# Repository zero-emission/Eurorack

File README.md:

# Eurorack
A collection of open hardware projects for Eurorack

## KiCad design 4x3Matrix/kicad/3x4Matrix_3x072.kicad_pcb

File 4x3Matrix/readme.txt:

A simple 4 in, 3 out Matrix mixer in 10HP.

It's designed to be an easy build as a first SMD project, with 0805 resistors with plenty of space inbetween.

The four inputs can be mixed in a three different ways for three different outputs.

The mixer is DC coupled, so can be used for both CV and audio.

Please double check IC orientation: TL072 pin 1 is down, TL074 pin 1 is up (Skewed side of the IC)
Some examples:

- Mix four cv signals to three different outputs
- Create feedback loops, patching one output back into an input. 
By patching multiple feedback loops you can create complex audio signals and waveshaping. 
Patching effects like delays inbetween can produce infinite feedback.

- For output A turn down input 3 and 4. For output B turn down input 1 and 2. Now you have two independent 2 channel mixers. 
You could use one as a CV attenuator and the other for mixing audio.

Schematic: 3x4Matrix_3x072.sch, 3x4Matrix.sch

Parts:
A_1, A_2, A_3, A_4: A100K; Potentiometer_Alpha_RD901F-40-00D_Single_Vertical
B_1, B_2, B_3, B_4: A100K; Potentiometer_Alpha_RD901F-40-00D_Single_Vertical
C1, C2: 10uF; CP_Radial_D5.0mm_P2.50mm
C3, C4, C5, C6, C7, C8: 100nF; C_0805_2012Metric
C_1, C_2, C_3, C_4: A100K; Potentiometer_Alpha_RD901F-40-00D_Single_Vertical
D1, D2: 1N4004; D_DO-41_SOD81_P10.16mm_Horizontal
IN1, IN2, IN3, IN4: AudioJack; Jack_3.5mm_QingPu_WQP-PJ398SM_Vertical_CircularHoles
OUTA1: AudioJack; Jack_3.5mm_QingPu_WQP-PJ398SM_Vertical_CircularHoles
OUTB1: AudioJack; Jack_3.5mm_QingPu_WQP-PJ398SM_Vertical_CircularHoles
OUTC1: AudioJack; Jack_3.5mm_QingPu_WQP-PJ398SM_Vertical_CircularHoles
R1, R2, R3, R4, R5, R6, R7, R8, R9, R10, R11, R12, R13, R14, R15, R16, R17, R18, R19, R20, R21: 100k; R_0805_2012Metric
R22, R23, R24: 1k; R_0805_2012Metric
SV2: EURO_POWER_HEADERREGULAR; PinHeader_2x05_P2.54mm_Vertical
U1, U2, U3: TL072_SMD; SOIC-8_3.9x4.9mm_P1.27mm

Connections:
/+12UP1: D1.2 (A), SV2.1, SV2.2
/-12UP1: D2.1 (K), SV2.9, SV2.10
/C-11: R3.1, R4.1, R9.2, R18.1, R21.1, U1.2 (-)
/N$1: A_3.2, R1.2
/N$2: B_3.2, R2.2
/N$3: C_3.2, R3.2
/N$4: C_2.2, R4.2
/N$5: B_2.2, R5.2
/N$6: A_2.2, R6.2
/N$7: B_1.2, R8.2
/N$8: C_1.2, R18.2
/N$9: A_1.2, R7.2
/N$10: A_4.3, B_4.3, C_4.3, IN4.T
/N$11: OUTC1.T, R22.1
/N$12: C1.2, C3.2, C5.2, C7.2, D2.2 (A), U1.4 (V-), U2.4 (V-), U3.4 (V-)
/N$13: A_4.2, R19.2
/N$14: B_4.2, R20.2
/N$15: C_4.2, R21.2
/N$16: OUTB1.T, R23.1
/N$17: OUTA1.T, R24.1
/N$18: R1.1, R6.1, R7.1, R15.2, R19.1, U3.2 (-)
/N$21: A_3.3, B_3.3, C_3.3, IN3.T
/N$22: A_2.3, B_2.3, C_2.3, IN2.T
/N$23: A_1.3, B_1.3, C_1.3, IN1.T
/N$24: R12.1, R13.2, U2.1
/N$25: R10.1, R11.2, U1.6 (-)
/N$26: R2.1, R5.1, R8.1, R12.2, R20.1, U2.2 (-)
/N$27: R11.1, R22.2, U1.7
/N$28: R13.1, R14.2, U2.6 (-)
/N$29: R14.1, R23.2, U2.7
/N$32: R16.1, R17.2, U3.6 (-)
/N$33: R17.1, R24.2, U3.7
/N$35: C2.1, C4.1, C6.1, C8.1, D1.1 (K), U1.8 (V+), U2.8 (V+), U3.8 (V+)
/PIN1: R9.1, R10.2, U1.1
/PINN1: R15.1, R16.2, U3.1
GND: A_1.1, A_2.1, A_3.1, A_4.1, B_1.1, B_2.1, B_3.1, B_4.1, C1.1, C2.2, C3.1, C4.2, C5.1, C6.2, C7.1, C8.2, C_1.1, C_2.1, C_3.1, C_4.1, IN1.S, IN2.S, IN3.S, IN4.S, OUTA1.S, OUTB1.S, OUTC1.S, SV2.3, SV2.4, SV2.5, SV2.6, SV2.7, SV2.8, U1.3 (+), U1.5 (+), U2.3 (+), U2.5 (+), U3.3 (+), U3.5 (+)

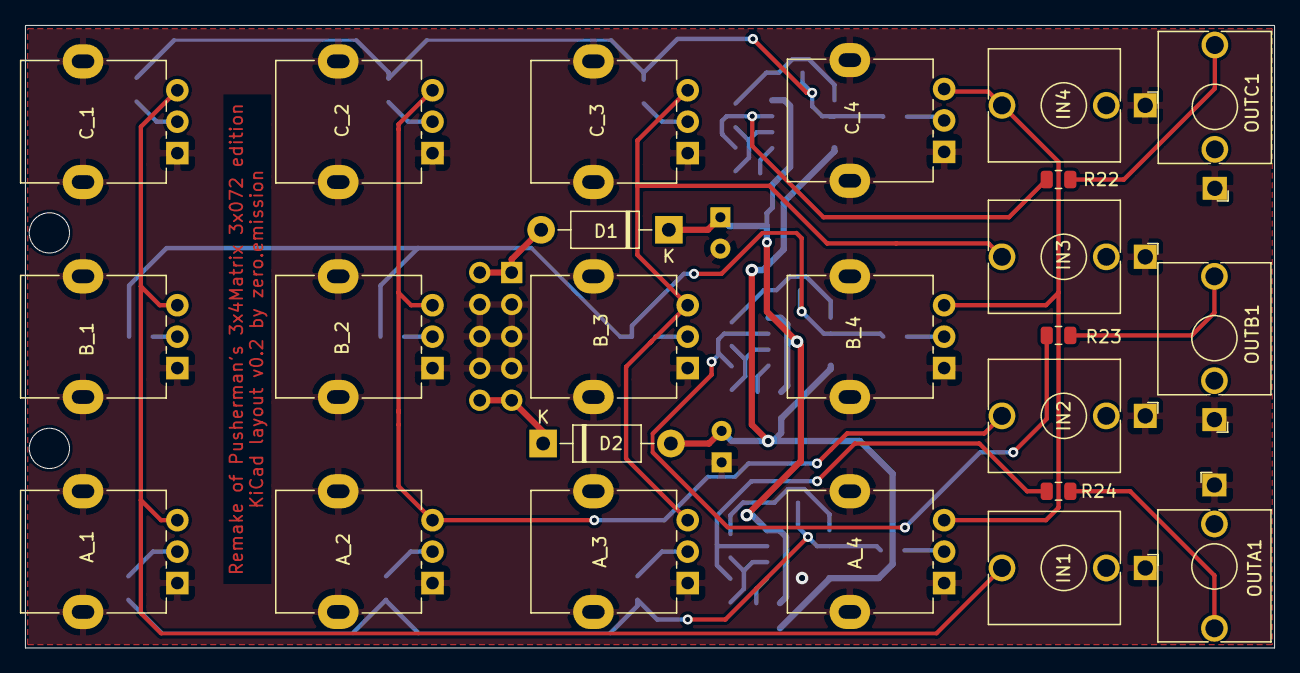
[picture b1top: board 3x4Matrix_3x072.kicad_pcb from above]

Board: 2 copper layers, 99.4 x 49.5 mm, 59 parts (0 on the bottom side), 36 nets.

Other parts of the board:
@HOLE0, @HOLE1: (no value)

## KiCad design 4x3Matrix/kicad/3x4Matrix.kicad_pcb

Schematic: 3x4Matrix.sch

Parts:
A1, A2, A3, A4: A100K; Potentiometer_Alpha_RD901F-40-00D_Single_Vertical
B1, B2, B3, B4: A100K; Potentiometer_Alpha_RD901F-40-00D_Single_Vertical
C1, C9, C10, C11: 100nF; SPARKFUN_0805
C7, C8: 10uF; SPARKFUN-CAPACITORS_CPOL-RADIAL-10UF-25V
C-1-34, C-2, C-3, C-4: A100K; Potentiometer_Alpha_RD901F-40-00D_Single_Vertical
D3, D4: 1N4004; _MOD_DIODE_DO41-10
M1, M2, M3, M4: AudioJack; Jack_3.5mm_QingPu_WQP-PJ398SM_Vertical_CircularHoles
MAA34: AudioJack; Jack_3.5mm_QingPu_WQP-PJ398SM_Vertical_CircularHoles
MB34: AudioJack; Jack_3.5mm_QingPu_WQP-PJ398SM_Vertical_CircularHoles
MCC34: AudioJack; Jack_3.5mm_QingPu_WQP-PJ398SM_Vertical_CircularHoles
R1, R2, R3, R4, R5, R6, R7, R8, R9, R10, R11, R12, R13, R14, R15, R16, R17, R18, R19, R20, R21: 100k; SPARKFUN-PASSIVES_0805
R22, R23, R24: 1k; SPARKFUN-PASSIVES_0805
SV2: EURO_POWER_HEADERREGULAR; PinHeader_2x05_P2.54mm_Vertical
U1: TL074_SMD; SOIC-14_3.9x8.7mm_P1.27mm
U2: TL072_SMD; SOIC-8_3.9x4.9mm_P1.27mm

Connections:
/+12UP1: D3.A, SV2.1, SV2.2
/-12UP1: D4.C, SV2.9, SV2.10
/C-11: R3.1, R4.1, R9.2, R18.1, R21.1, U1.2
/N$1: A3.2, R1.2
/N$2: B3.2, R2.2
/N$3: C-3.2, R3.2
/N$4: C-2.2, R4.2
/N$5: B2.2, R5.2
/N$6: A2.2, R6.2
/N$7: B1.2, R8.2
/N$8: C-1-34.2, R18.2
/N$9: A1.2, R7.2
/N$10: A4.3, B4.3, C-4.3, M4.T
/N$11: MCC34.T, R22.1
/N$12: C1.2, C8.2, C10.2, D4.A, U1.11, U2.4 (V-)
/N$13: A4.2, R19.2
/N$14: B4.2, R20.2
/N$15: C-4.2, R21.2
/N$16: MB34.T, R23.1
/N$17: MAA34.T, R24.1
/N$18: R1.1, R6.1, R7.1, R15.2, R19.1, U2.2 (-)
/N$21: A3.3, B3.3, C-3.3, M3.T
/N$22: A2.3, B2.3, C-2.3, M2.T
/N$23: A1.3, B1.3, C-1-34.3, M1.T
/N$24: R12.1, R13.2, U1.8
/N$25: R10.1, R11.2, U1.6
/N$26: R2.1, R5.1, R8.1, R12.2, R20.1, U1.9
/N$27: R11.1, R22.2, U1.7
/N$28: R13.1, R14.2, U1.13
/N$29: R14.1, R23.2, U1.14
/N$32: R16.1, R17.2, U2.6 (-)
/N$33: R17.1, R24.2, U2.7
/N$35: C7.1, C9.1, C11.1, D3.C, U1.4, U2.8 (V+)
/PIN1: R9.1, R10.2, U1.1
/PINN1: R15.1, R16.2, U2.1
GND: A1.1, A2.1, A3.1, A4.1, B1.1, B2.1, B3.1, B4.1, C1.1, C7.2, C8.1, C9.2, C10.1, C11.2, C-1-34.1, C-2.1, C-3.1, C-4.1, M1.S, M2.S, M3.S, M4.S, MAA34.S, MB34.S, MCC34.S, SV2.3, SV2.4, SV2.5, SV2.6, SV2.7, SV2.8, U1.3, U1.5, U1.10, U1.12, U2.3 (+), U2.5 (+)

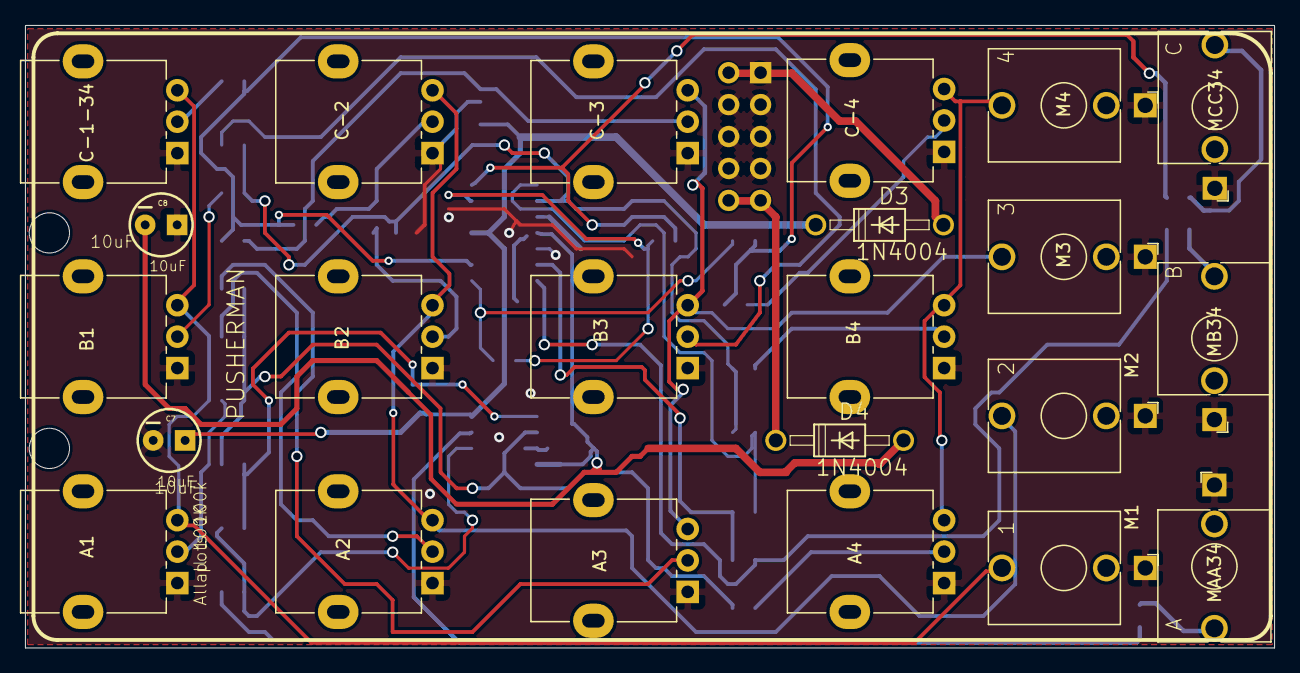
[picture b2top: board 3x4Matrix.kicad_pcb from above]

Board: 2 copper layers, 99.4 x 49.5 mm, 56 parts (0 on the bottom side), 36 nets.

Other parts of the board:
@HOLE0, @HOLE1: (no value)

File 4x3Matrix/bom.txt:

All resistors 100k except for the three 1k output resistors.

If you like you can change the A B and C gain resistors marked on the pcb to a different value, for higher or lower gain.

Default 100k is unity gain.

_________
BOM

12x 9mm 100K potmeter  (I use tall trimmer pots, regular pots with knobs are too large)
7x Thonkiconn jack
1x Power header
Part     Value                    Package              

C1       100nF                    0805                 
C7       10uF                     CPOL-RADIAL-10UF-35V 
C8       10uF                     CPOL-RADIAL-10UF-35V 
C9       100nF                    0805                 
C10      100nF                    0805                 
C11      100nF                    0805                 
D3       1N4004                   DO41-10              
D4       1N4004                   DO41-10              

R1-R21   100k                     0805                 
R22-24   1k                       0805                 
U1       TL074_SMD                SO14     
U2       TL072_SMD                SO08

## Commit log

2017-11-08 Create readme.txt
    Some info about the module
2017-11-08 Create bom.txt
    Part list
2017-11-08 Add files via upload
    The gerber files
2017-11-08 Add files via upload
    Eagle files
2017-11-08 Add files via upload
    A photo of the module
2018-07-27 small note
2020-07-05 Conversion of Eagle files to KiCad current version 5.1.6. Work in progress, critical components already replaced by native KiCad library entities.
2020-07-18 All library parts replaced by default Kicad, new version created which uses 3 TL072 instead of TL072 + TL074 to eliminate crosstalk
2020-07-19 Corrections made to ground planes, trace widths, etc. after visual checks of printout

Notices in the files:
parts and their libraries:
SparkFun-Capacitors: Licensing: Creative Commons ShareAlike 4.0 International - https://creativecommons.org/licenses/by-sa/4.0
